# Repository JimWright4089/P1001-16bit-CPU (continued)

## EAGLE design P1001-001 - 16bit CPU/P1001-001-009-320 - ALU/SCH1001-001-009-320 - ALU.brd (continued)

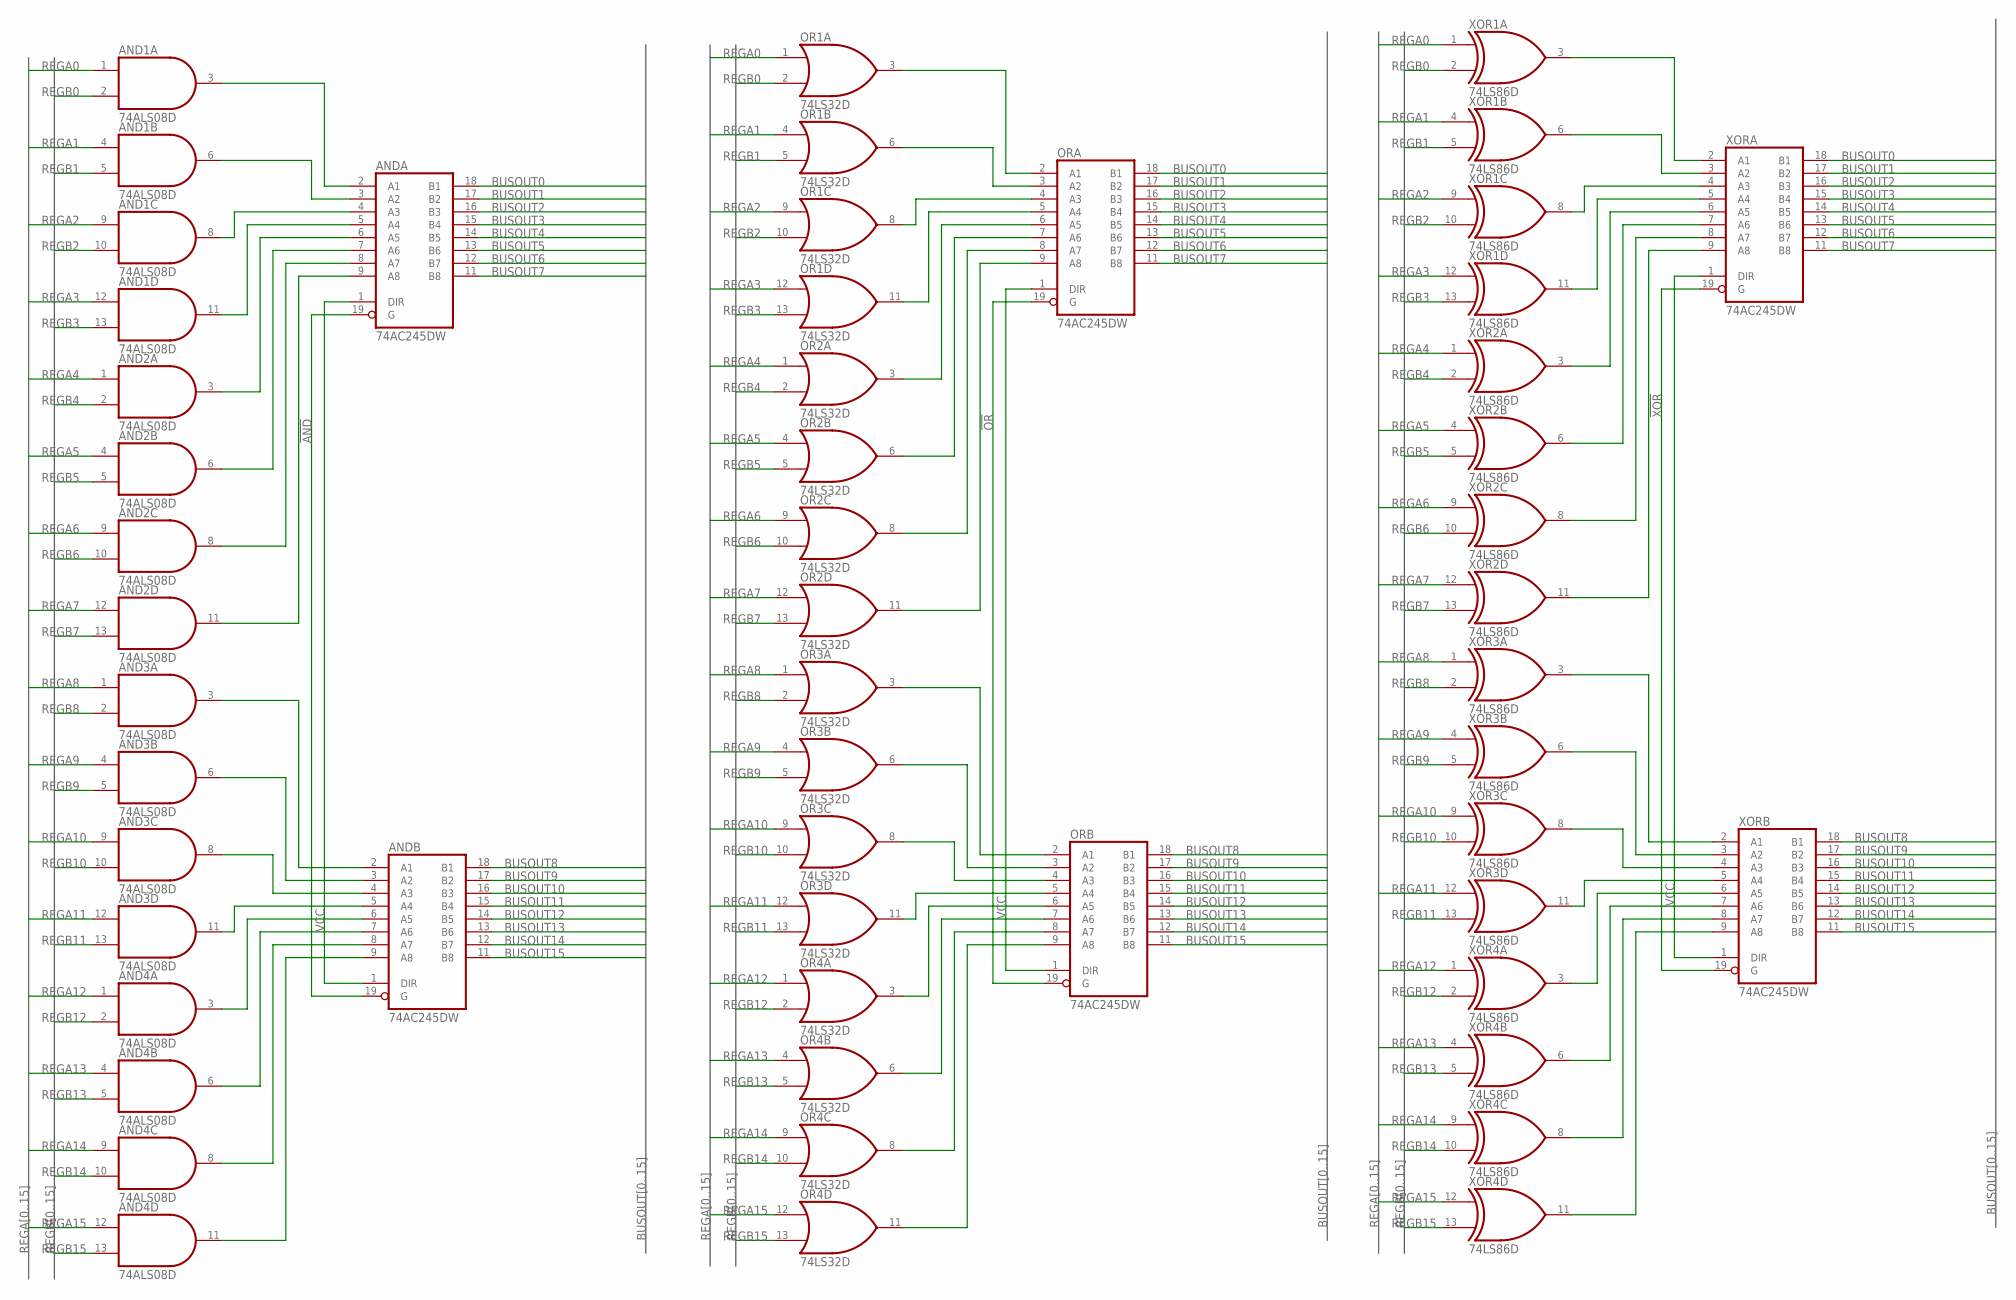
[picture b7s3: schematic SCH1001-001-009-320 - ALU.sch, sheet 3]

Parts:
AND1, AND2, AND3, AND4: 74ALS08D; SO14
ANDA: 74AC245DW; SO20W
ANDB: 74AC245DW; SO20W
OR1, OR2, OR3, OR4: 74LS32D; SO14
ORA: 74AC245DW; SO20W
ORB: 74AC245DW; SO20W
XOR1, XOR2, XOR3, XOR4: 74LS86D; SO14
XORA: 74AC245DW; SO20W
XORB: 74AC245DW; SO20W

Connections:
!AND: ANDA.19 (G), ANDB.19 (G); also elsewhere on the board
!OR: ORA.19 (G), ORB.19 (G); also elsewhere on the board
!XOR: XORA.19 (G), XORB.19 (G); also elsewhere on the board
BUSOUT0: ANDA.18 (B1), ORA.18 (B1), XORA.18 (B1); also elsewhere on the board
BUSOUT1: ANDA.17 (B2), ORA.17 (B2), XORA.17 (B2); also elsewhere on the board
BUSOUT2: ANDA.16 (B3), ORA.16 (B3), XORA.16 (B3); also elsewhere on the board
BUSOUT3: ANDA.15 (B4), ORA.15 (B4), XORA.15 (B4); also elsewhere on the board
BUSOUT4: ANDA.14 (B5), ORA.14 (B5), XORA.14 (B5); also elsewhere on the board
BUSOUT5: ANDA.13 (B6), ORA.13 (B6), XORA.13 (B6); also elsewhere on the board
BUSOUT6: ANDA.12 (B7), ORA.12 (B7), XORA.12 (B7); also elsewhere on the board
BUSOUT7: ANDA.11 (B8), ORA.11 (B8), XORA.11 (B8); also elsewhere on the board
BUSOUT8: ANDB.18 (B1), ORB.18 (B1), XORB.18 (B1); also elsewhere on the board
BUSOUT9: ANDB.17 (B2), ORB.17 (B2), XORB.17 (B2); also elsewhere on the board
BUSOUT10: ANDB.16 (B3), ORB.16 (B3), XORB.16 (B3); also elsewhere on the board
BUSOUT11: ANDB.15 (B4), ORB.15 (B4), XORB.15 (B4); also elsewhere on the board
BUSOUT12: ANDB.14 (B5), ORB.14 (B5), XORB.14 (B5); also elsewhere on the board
BUSOUT13: ANDB.13 (B6), ORB.13 (B6), XORB.13 (B6); also elsewhere on the board
BUSOUT14: ANDB.12 (B7), ORB.12 (B7), XORB.12 (B7); also elsewhere on the board
BUSOUT15: ANDB.11 (B8), ORB.11 (B8), XORB.11 (B8); also elsewhere on the board
GND: AND1.7 (GND), AND2.7 (GND), AND3.7 (GND), AND4.7 (GND), ANDA.10 (GND), ANDB.10 (GND), OR1.7 (GND), OR2.7 (GND), OR3.7 (GND), OR4.7 (GND), ORA.10 (GND), ORB.10 (GND), XOR1.7 (GND), XOR2.7 (GND), XOR3.7 (GND), XOR4.7 (GND), XORA.10 (GND), XORB.10 (GND); also elsewhere on the board
unnamed: AND1.3 (O), ANDA.2 (A1)
unnamed: AND1.6 (O), ANDA.3 (A2)
unnamed: AND1.8 (O), ANDA.4 (A3)
unnamed: AND1.11 (O), ANDA.5 (A4)
unnamed: AND2.3 (O), ANDA.6 (A5)
unnamed: AND2.6 (O), ANDA.7 (A6)
unnamed: AND2.8 (O), ANDA.8 (A7)
unnamed: AND2.11 (O), ANDA.9 (A8)
unnamed: AND3.3 (O), ANDB.2 (A1)
unnamed: AND3.6 (O), ANDB.3 (A2)
unnamed: AND3.8 (O), ANDB.4 (A3)
unnamed: AND3.11 (O), ANDB.5 (A4)
unnamed: AND4.3 (O), ANDB.6 (A5)
unnamed: AND4.6 (O), ANDB.7 (A6)
unnamed: AND4.8 (O), ANDB.8 (A7)
unnamed: AND4.11 (O), ANDB.9 (A8)
unnamed: OR1.3 (O), ORA.2 (A1)
unnamed: OR1.6 (O), ORA.3 (A2)
unnamed: OR1.8 (O), ORA.4 (A3)
unnamed: OR1.11 (O), ORA.5 (A4)
unnamed: OR2.3 (O), ORA.6 (A5)
unnamed: OR2.6 (O), ORA.7 (A6)
unnamed: OR2.8 (O), ORA.8 (A7)
unnamed: OR2.11 (O), ORA.9 (A8)
unnamed: OR3.3 (O), ORB.2 (A1)
unnamed: OR3.6 (O), ORB.3 (A2)
unnamed: OR3.8 (O), ORB.4 (A3)
unnamed: OR3.11 (O), ORB.5 (A4)
unnamed: OR4.3 (O), ORB.6 (A5)
unnamed: OR4.6 (O), ORB.7 (A6)
unnamed: OR4.8 (O), ORB.8 (A7)
unnamed: OR4.11 (O), ORB.9 (A8)
unnamed: XOR1.3 (O), XORA.2 (A1)
unnamed: XOR1.6 (O), XORA.3 (A2)
unnamed: XOR1.8 (O), XORA.4 (A3)
unnamed: XOR1.11 (O), XORA.5 (A4)
unnamed: XOR2.3 (O), XORA.6 (A5)
unnamed: XOR2.6 (O), XORA.7 (A6)
unnamed: XOR2.8 (O), XORA.8 (A7)
unnamed: XOR2.11 (O), XORA.9 (A8)
unnamed: XOR3.3 (O), XORB.2 (A1)
unnamed: XOR3.6 (O), XORB.3 (A2)
unnamed: XOR3.8 (O), XORB.4 (A3)
unnamed: XOR3.11 (O), XORB.5 (A4)
unnamed: XOR4.3 (O), XORB.6 (A5)
unnamed: XOR4.6 (O), XORB.7 (A6)
unnamed: XOR4.8 (O), XORB.8 (A7)
unnamed: XOR4.11 (O), XORB.9 (A8)
REGA0: AND1.1 (I0), OR1.1 (I0), XOR1.1 (I0); also elsewhere on the board
REGA1: AND1.4 (I0), OR1.4 (I0), XOR1.4 (I0); also elsewhere on the board
REGA2: AND1.9 (I0), OR1.9 (I0), XOR1.9 (I0); also elsewhere on the board
REGA3: AND1.12 (I0), OR1.12 (I0), XOR1.12 (I0); also elsewhere on the board
REGA4: AND2.1 (I0), OR2.1 (I0), XOR2.1 (I0); also elsewhere on the board
REGA5: AND2.4 (I0), OR2.4 (I0), XOR2.4 (I0); also elsewhere on the board
REGA6: AND2.9 (I0), OR2.9 (I0), XOR2.9 (I0); also elsewhere on the board
REGA7: AND2.12 (I0), OR2.12 (I0), XOR2.12 (I0); also elsewhere on the board
REGA8: AND3.1 (I0), OR3.1 (I0), XOR3.1 (I0); also elsewhere on the board
REGA9: AND3.4 (I0), OR3.4 (I0), XOR3.4 (I0); also elsewhere on the board
REGA10: AND3.9 (I0), OR3.9 (I0), XOR3.9 (I0); also elsewhere on the board
REGA11: AND3.12 (I0), OR3.12 (I0), XOR3.12 (I0); also elsewhere on the board
REGA12: AND4.1 (I0), OR4.1 (I0), XOR4.1 (I0); also elsewhere on the board
REGA13: AND4.4 (I0), OR4.4 (I0), XOR4.4 (I0); also elsewhere on the board
REGA14: AND4.9 (I0), OR4.9 (I0), XOR4.9 (I0); also elsewhere on the board
REGA15: AND4.12 (I0), OR4.12 (I0), XOR4.12 (I0); also elsewhere on the board
REGB0: AND1.2 (I1), OR1.2 (I1), XOR1.2 (I1); also elsewhere on the board
REGB1: AND1.5 (I1), OR1.5 (I1), XOR1.5 (I1); also elsewhere on the board
REGB2: AND1.10 (I1), OR1.10 (I1), XOR1.10 (I1); also elsewhere on the board
REGB3: AND1.13 (I1), OR1.13 (I1), XOR1.13 (I1); also elsewhere on the board
REGB4: AND2.2 (I1), OR2.2 (I1), XOR2.2 (I1); also elsewhere on the board
REGB5: AND2.5 (I1), OR2.5 (I1), XOR2.5 (I1); also elsewhere on the board
REGB6: AND2.10 (I1), OR2.10 (I1), XOR2.10 (I1); also elsewhere on the board
REGB7: AND2.13 (I1), OR2.13 (I1), XOR2.13 (I1); also elsewhere on the board
REGB8: AND3.2 (I1), OR3.2 (I1), XOR3.2 (I1); also elsewhere on the board
REGB9: AND3.5 (I1), OR3.5 (I1), XOR3.5 (I1); also elsewhere on the board
REGB10: AND3.10 (I1), OR3.10 (I1), XOR3.10 (I1); also elsewhere on the board
REGB11: AND3.13 (I1), OR3.13 (I1), XOR3.13 (I1); also elsewhere on the board
REGB12: AND4.2 (I1), OR4.2 (I1), XOR4.2 (I1); also elsewhere on the board
REGB13: AND4.5 (I1), OR4.5 (I1), XOR4.5 (I1); also elsewhere on the board
REGB14: AND4.10 (I1), OR4.10 (I1), XOR4.10 (I1); also elsewhere on the board
REGB15: AND4.13 (I1), OR4.13 (I1), XOR4.13 (I1); also elsewhere on the board
VCC: AND1.14 (VCC), AND2.14 (VCC), AND3.14 (VCC), AND4.14 (VCC), ANDA.1 (DIR), ANDA.20 (VCC), ANDB.1 (DIR), ANDB.20 (VCC), OR1.14 (VCC), OR2.14 (VCC), OR3.14 (VCC), OR4.14 (VCC), ORA.1 (DIR), ORA.20 (VCC), ORB.1 (DIR), ORB.20 (VCC), XOR1.14 (VCC), XOR2.14 (VCC), XOR3.14 (VCC), XOR4.14 (VCC), XORA.1 (DIR), XORA.20 (VCC), XORB.1 (DIR), XORB.20 (VCC); also elsewhere on the board

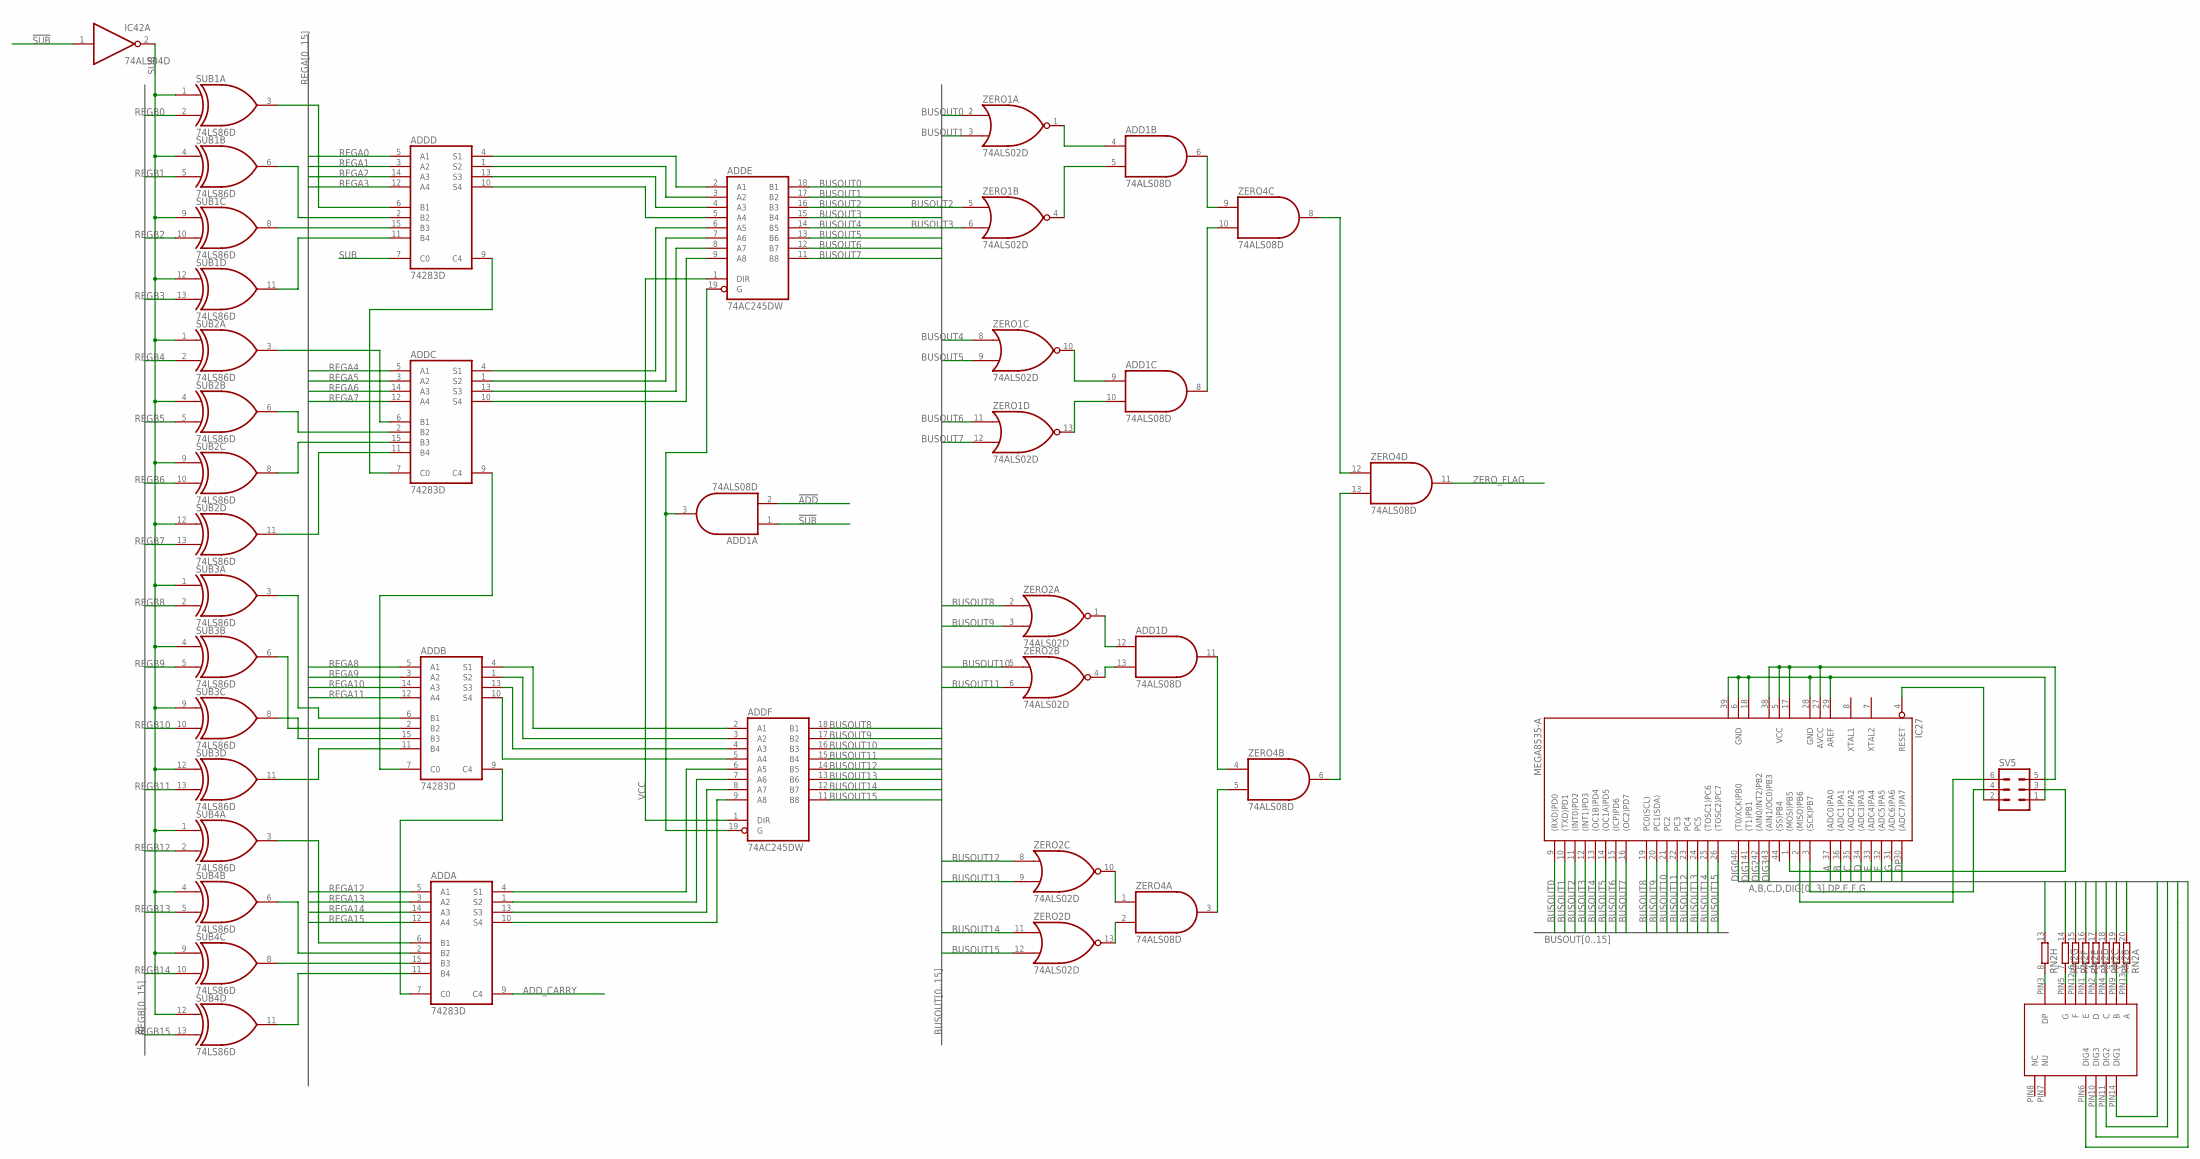
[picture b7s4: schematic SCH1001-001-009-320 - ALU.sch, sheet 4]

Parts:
ADD1: 74ALS08D; SO14
ADDA: 74283D; SO16
ADDB: 74283D; SO16
ADDC: 74283D; SO16
ADDD: 74283D; SO16
ADDE: 74AC245DW; SO20W
ADDF: 74AC245DW; SO20W
IC27: MEGA8535-A; TQFP44
IC42: 74ALS04D; SO14
RN2: 10R-NSOMC; SOMC20
SUB1, SUB2, SUB3, SUB4: 74LS86D; SO14
SV5: ML6
U$1: 4-DIGIT-7-SEGMENT
ZERO1, ZERO2: 74ALS02D; SO14
ZERO4: 74ALS08D; SO14

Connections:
!ADD: ADD1.2 (I1); also elsewhere on the board
!SUB: ADD1.1 (I0), IC42.1 (I); also elsewhere on the board
A: IC27.37 ((ADC0)PA0), RN2.20 (2)
ADD_CARRY: ADDA.9 (C4); also elsewhere on the board
B: IC27.36 ((ADC1)PA1), RN2.19 (2)
BUSOUT0: ADDE.18 (B1), IC27.9 ((RXD)PD0), ZERO1.2 (I0); also elsewhere on the board
BUSOUT1: ADDE.17 (B2), IC27.10 ((TXD)PD1), ZERO1.3 (I1); also elsewhere on the board
BUSOUT2: ADDE.16 (B3), IC27.11 ((INT0)PD2), ZERO1.5 (I0); also elsewhere on the board
BUSOUT3: ADDE.15 (B4), IC27.12 ((INT1)PD3), ZERO1.6 (I1); also elsewhere on the board
BUSOUT4: ADDE.14 (B5), IC27.13 ((OC1B)PD4), ZERO1.8 (I0); also elsewhere on the board
BUSOUT5: ADDE.13 (B6), IC27.14 ((OC1A)PD5), ZERO1.9 (I1); also elsewhere on the board
BUSOUT6: ADDE.12 (B7), IC27.15 ((ICP)PD6), ZERO1.11 (I0); also elsewhere on the board
BUSOUT7: ADDE.11 (B8), IC27.16 ((OC2)PD7), ZERO1.12 (I1); also elsewhere on the board
BUSOUT8: ADDF.18 (B1), IC27.19 (PC0(SCL)), ZERO2.2 (I0); also elsewhere on the board
BUSOUT9: ADDF.17 (B2), IC27.20 (PC1(SDA)), ZERO2.3 (I1); also elsewhere on the board
BUSOUT10: ADDF.16 (B3), IC27.21 (PC2), ZERO2.5 (I0); also elsewhere on the board
BUSOUT11: ADDF.15 (B4), IC27.22 (PC3), ZERO2.6 (I1); also elsewhere on the board
BUSOUT12: ADDF.14 (B5), IC27.23 (PC4), ZERO2.8 (I0); also elsewhere on the board
BUSOUT13: ADDF.13 (B6), IC27.24 (PC5), ZERO2.9 (I1); also elsewhere on the board
BUSOUT14: ADDF.12 (B7), IC27.25 ((TOSC1)PC6), ZERO2.11 (I0); also elsewhere on the board
BUSOUT15: ADDF.11 (B8), IC27.26 ((TOSC2)PC7), ZERO2.12 (I1); also elsewhere on the board
C: IC27.35 ((ADC2)PA2), RN2.18 (2)
D: IC27.34 ((ADC3)PA3), RN2.17 (2)
DIG0: IC27.40 ((T0/XCK)PB0), U$1.PIN14 (DIG1)
DIG1: IC27.41 ((T1)PB1), U$1.PIN11 (DIG2)
DIG2: IC27.42 ((AIN0/INT2)PB2), U$1.PIN10 (DIG3)
DIG3: IC27.43 ((AIN1/OC0)PB3), U$1.PIN6 (DIG4)
DP: IC27.30 ((ADC7)PA7), RN2.13 (2)
E: IC27.33 ((ADC4)PA4), RN2.16 (2)
F: IC27.32 ((ADC5)PA5), RN2.15 (2)
G: IC27.31 ((ADC6)PA6), RN2.14 (2)
GND: ADD1.7 (GND), ADDA.8 (GND), ADDB.8 (GND), ADDC.8 (GND), ADDD.8 (GND), ADDE.10 (GND), ADDF.10 (GND), IC42.7 (GND), SUB1.7 (GND), SUB2.7 (GND), SUB3.7 (GND), SUB4.7 (GND), ZERO1.7 (GND), ZERO2.7 (GND), ZERO4.7 (GND); also elsewhere on the board
unnamed: ADDD.6 (B1), SUB1.3 (O)
unnamed: ADDD.2 (B2), SUB1.6 (O)
unnamed: ADDD.15 (B3), SUB1.8 (O)
unnamed: ADDD.11 (B4), SUB1.11 (O)
unnamed: ADDD.4 (S1), ADDE.2 (A1)
unnamed: ADDD.1 (S2), ADDE.3 (A2)
unnamed: ADDC.10 (S4), ADDE.9 (A8)
unnamed: ADDC.13 (S3), ADDE.8 (A7)
unnamed: ADDC.1 (S2), ADDE.7 (A6)
unnamed: ADDC.4 (S1), ADDE.6 (A5)
unnamed: ADDC.6 (B1), SUB2.3 (O)
unnamed: ADDC.2 (B2), SUB2.6 (O)
unnamed: ADDC.15 (B3), SUB2.8 (O)
unnamed: ADDC.11 (B4), SUB2.11 (O)
unnamed: ADDC.7 (C0), ADDD.9 (C4)
unnamed: ADDA.2 (B2), SUB4.6 (O)
unnamed: ADDA.15 (B3), SUB4.8 (O)
unnamed: ADDA.11 (B4), SUB4.11 (O)
unnamed: ADDA.6 (B1), SUB4.3 (O)
unnamed: ADDA.7 (C0), ADDB.9 (C4)
unnamed: ADDA.10 (S4), ADDF.9 (A8)
unnamed: ADDA.13 (S3), ADDF.8 (A7)
unnamed: ADDA.1 (S2), ADDF.7 (A6)
unnamed: ADDA.4 (S1), ADDF.6 (A5)
unnamed: ADDB.11 (B4), SUB3.11 (O)
unnamed: ADDB.15 (B3), SUB3.8 (O)
unnamed: ADDB.2 (B2), SUB3.6 (O)
unnamed: ADDB.6 (B1), SUB3.3 (O)
unnamed: ADDB.7 (C0), ADDC.9 (C4)
unnamed: ADDB.10 (S4), ADDF.5 (A4)
unnamed: ADDB.13 (S3), ADDF.4 (A3)
unnamed: ADDB.1 (S2), ADDF.3 (A2)
unnamed: ADDB.4 (S1), ADDF.2 (A1)
unnamed: ADD1.3 (O), ADDE.19 (G), ADDF.19 (G)
unnamed: ADD1.4 (I0), ZERO1.1 (O)
unnamed: ADD1.5 (I1), ZERO1.4 (O)
unnamed: ADD1.9 (I0), ZERO1.10 (O)
unnamed: ADD1.10 (I1), ZERO1.13 (O)
unnamed: ADD1.8 (O), ZERO4.10 (I1)
unnamed: ADD1.6 (O), ZERO4.9 (I0)
unnamed: ZERO4.8 (O), ZERO4.12 (I0)
unnamed: ZERO4.6 (O), ZERO4.13 (I1)
unnamed: ADD1.11 (O), ZERO4.4 (I0)
unnamed: ZERO4.3 (O), ZERO4.5 (I1)
unnamed: ZERO2.10 (O), ZERO4.1 (I0)
unnamed: ZERO2.13 (O), ZERO4.2 (I1)
unnamed: ADD1.12 (I0), ZERO2.1 (O)
unnamed: ADD1.13 (I1), ZERO2.4 (O)
unnamed: ADDD.13 (S3), ADDE.4 (A3)
unnamed: ADDD.10 (S4), ADDE.5 (A4)
unnamed: IC27.1 ((MOSI)PB5), SV5.3
unnamed: IC27.3 ((SCK)PB7), SV5.4
unnamed: IC27.2 ((MISO)PB6), SV5.6
unnamed: IC27.4 (RESET), SV5.2
unnamed: RN2.1, U$1.PIN13 (A)
unnamed: RN2.2 (1), U$1.PIN9 (B)
unnamed: RN2.3 (1), U$1.PIN4 (C)
unnamed: RN2.4 (1), U$1.PIN2 (D)
unnamed: RN2.5 (1), U$1.PIN1 (E)
unnamed: RN2.6 (1), U$1.PIN12 (F)
unnamed: RN2.7 (1), U$1.PIN5 (G)
unnamed: RN2.8 (1), U$1.PIN3 (DP)
unnamed: IC27.5 (VCC), IC27.17 (VCC1), IC27.27 (AVCC), IC27.38 (VCC2), SV5.5
unnamed: IC27.6 (GND), IC27.18 (GND1), IC27.28 (GND), IC27.29 (AREF), IC27.39 (GND2), SV5.1
REGA0: ADDD.5 (A1); also elsewhere on the board
REGA1: ADDD.3 (A2); also elsewhere on the board
REGA2: ADDD.14 (A3); also elsewhere on the board
REGA3: ADDD.12 (A4); also elsewhere on the board
REGA4: ADDC.5 (A1); also elsewhere on the board
REGA5: ADDC.3 (A2); also elsewhere on the board
REGA6: ADDC.14 (A3); also elsewhere on the board
REGA7: ADDC.12 (A4); also elsewhere on the board
REGA8: ADDB.5 (A1); also elsewhere on the board
REGA9: ADDB.3 (A2); also elsewhere on the board
REGA10: ADDB.14 (A3); also elsewhere on the board
REGA11: ADDB.12 (A4); also elsewhere on the board
REGA12: ADDA.5 (A1); also elsewhere on the board
REGA13: ADDA.3 (A2); also elsewhere on the board
REGA14: ADDA.14 (A3); also elsewhere on the board
REGA15: ADDA.12 (A4); also elsewhere on the board
REGB0: SUB1.2 (I1); also elsewhere on the board
REGB1: SUB1.5 (I1); also elsewhere on the board
REGB2: SUB1.10 (I1); also elsewhere on the board
REGB3: SUB1.13 (I1); also elsewhere on the board
REGB4: SUB2.2 (I1); also elsewhere on the board
REGB5: SUB2.5 (I1); also elsewhere on the board
REGB6: SUB2.10 (I1); also elsewhere on the board
REGB7: SUB2.13 (I1); also elsewhere on the board
REGB8: SUB3.2 (I1); also elsewhere on the board
REGB9: SUB3.5 (I1); also elsewhere on the board
REGB10: SUB3.10 (I1); also elsewhere on the board
REGB11: SUB3.13 (I1); also elsewhere on the board
REGB12: SUB4.2 (I1); also elsewhere on the board
REGB13: SUB4.5 (I1); also elsewhere on the board
REGB14: SUB4.10 (I1); also elsewhere on the board
REGB15: SUB4.13 (I1); also elsewhere on the board
SUB: ADDD.7 (C0), IC42.2 (O), SUB1.1 (I0), SUB1.4 (I0), SUB1.9 (I0), SUB1.12 (I0), SUB2.1 (I0), SUB2.4 (I0), SUB2.9 (I0), SUB2.12 (I0), SUB3.1 (I0), SUB3.4 (I0), SUB3.9 (I0), SUB3.12 (I0), SUB4.1 (I0), SUB4.4 (I0), SUB4.9 (I0), SUB4.12 (I0)
VCC: ADD1.14 (VCC), ADDA.16 (VCC), ADDB.16 (VCC), ADDC.16 (VCC), ADDD.16 (VCC), ADDE.1 (DIR), ADDE.20 (VCC), ADDF.1 (DIR), ADDF.20 (VCC), IC42.14 (VCC), SUB1.14 (VCC), SUB2.14 (VCC), SUB3.14 (VCC), SUB4.14 (VCC), ZERO1.14 (VCC), ZERO2.14 (VCC), ZERO4.14 (VCC); also elsewhere on the board
ZERO_FLAG: ZERO4.11 (O); also elsewhere on the board

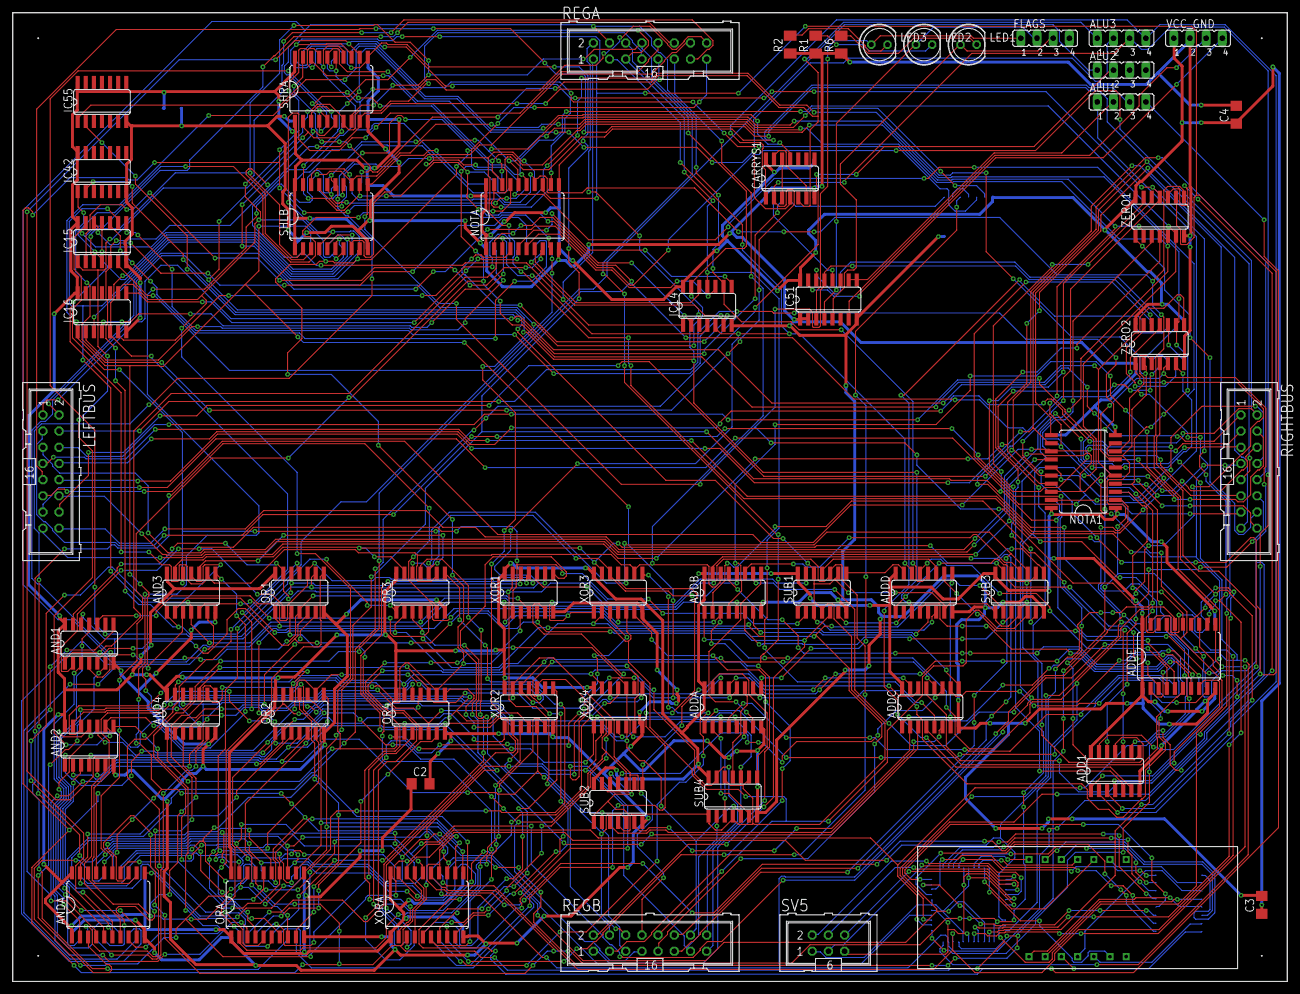
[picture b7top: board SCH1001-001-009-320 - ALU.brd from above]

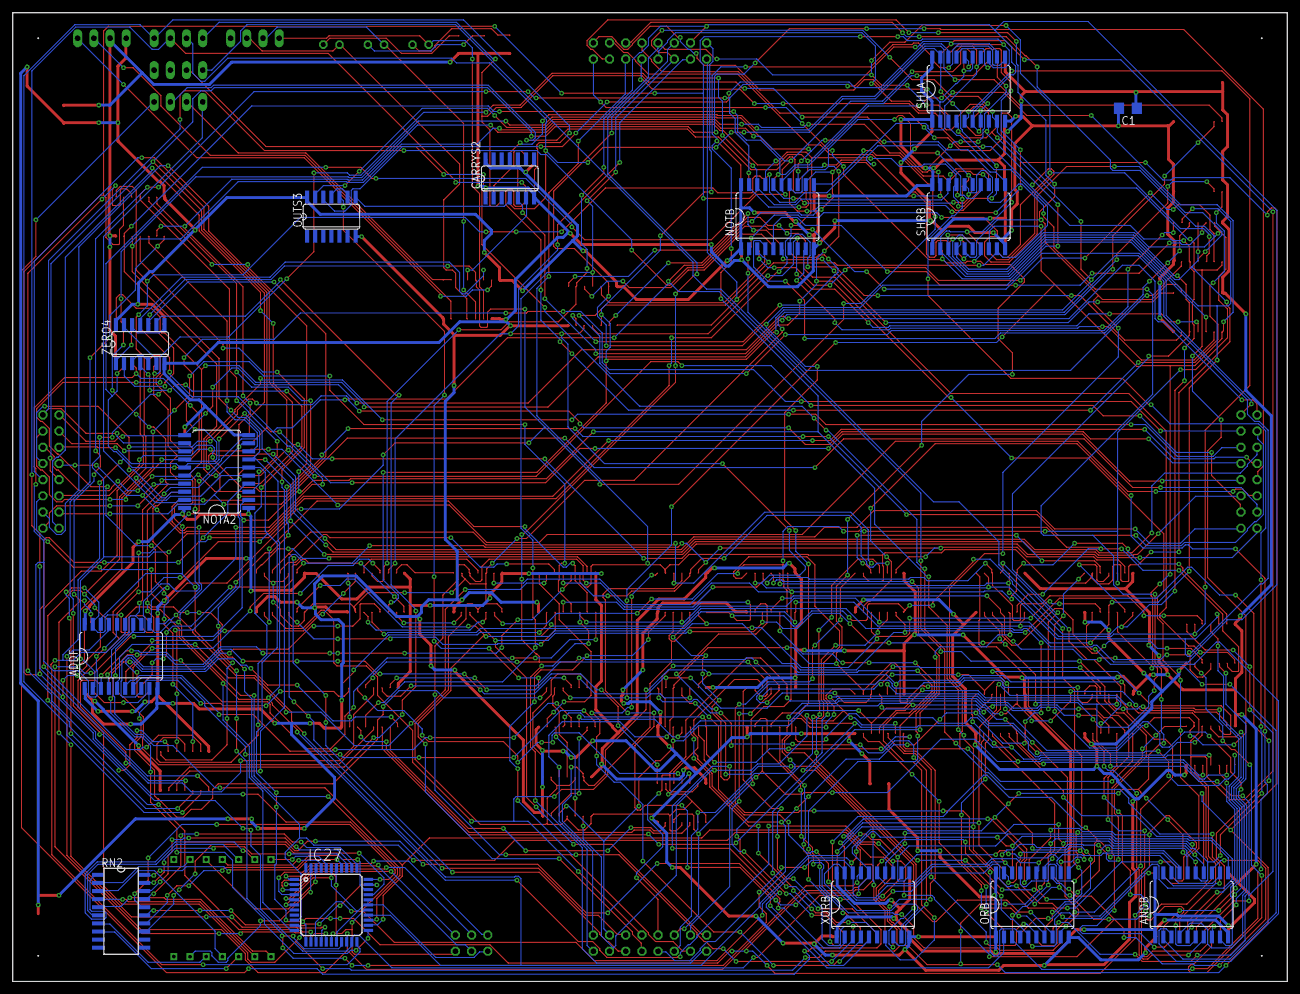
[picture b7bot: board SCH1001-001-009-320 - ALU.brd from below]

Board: 2 copper layers, 200.0 x 152.0 mm, 72 parts (14 on the bottom side), 236 nets.
